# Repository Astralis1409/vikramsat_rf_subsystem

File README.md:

# VikramSAT RF Board
VikramSAT RF Board is the main communications board for the 'vikramsat', which is a 2U cubesat that me and my teammates are trying to make. This board also includes the RP2350A as the main data processing IC along with multiple interfaces. 

The RF transmitter on this board has an output Power of 4 Watts and it is not recommend to use this without a ham radio license. although you can receive data just fine.

It uses the CC1125 RF Transceiver from Texas Instruments as it's Transceiver and GSQ5111 Power Amplifier and it operates in the 70cm band. the RP2350A acts as a control IC for the CC1125 and this simplifies the process for the OnBoard Computer(the OBC of the cubesat)

# Why I chose to make this project
Me and my friends got an idea of making a cubesat about this time last year, and started learning all the electronics and design, and i am the leader of the group and i design the communications part. I chose to make this project in highway because this was the perfect time, as i was thinking about starting to make the pcb anf highway was announced, and surprisingly, only 4 hours are left from now until highway ends forever!

# Images
Kicanvas Link: [Here](https://kicanvas.org/?github=https%3A%2F%2Fgithub.com%2FKeyaan-07%2FVikramSat-RF-subsystem%2Ftree%2Fmain%2Fhardware_rf)

Files now have .STEP files!

# BOM
Final Breakdown at the bottom
|Id |Designator                                           |Designation                |Footprint                               |DNO|Price |Quantity|Amount |Link                                                                                                                                                                                        |
|---|-----------------------------------------------------|---------------------------|----------------------------------------|---|------|--------|-------|--------------------------------------------------------------------------------------------------------------------------------------------------------------------------------------------|
|1  |C1, C2, C32, C33                                     |15p                        |402                                     |Yes|0     |4       |0      |https://lcsc.com/product-detail/Multilayer-Ceramic-Capacitors-MLCC-SMD-SMT_Murata-Electronics-GJM1555C1H150FB01D_C441742.html                                                               |
|2  |C10                                                  |10n                        |402                                     |No |0.0008|100     |0.08   |https://lcsc.com/product-detail/Multilayer-Ceramic-Capacitors-MLCC-SMD-SMT_CCTC-TCC0402X7R103K500AT_C688874.html                                                                            |
|3  |C11, C12, C13, C15, C16, C3, C4, C5, C6, C7, C9      |47n                        |402                                     |No |0.0008|100     |0.08   |https://lcsc.com/product-detail/Multilayer-Ceramic-Capacitors-MLCC-SMD-SMT_CCTC-TCC0402X7R473M250AT_C5142571.html                                                                           |
|4  |C14                                                  |220n                       |402                                     |No |0.0016|100     |0.16   |https://lcsc.com/product-detail/Multilayer-Ceramic-Capacitors-MLCC-SMD-SMT_HRE-CGA0402X5R224K100GT_C7503518.html                                                                            |
|5  |C17, C18, C19, C21, C34, C35, C36, C39, C40          |4.7u                       |402                                     |No |0.014 |50      |0.7    |https://lcsc.com/product-detail/Multilayer-Ceramic-Capacitors-MLCC-SMD-SMT_Chinocera-HGC0402R5475M250NTEJ_C22367824.html                                                                    |
|6  |C20, C22, C23, C24, C25, C26, C27, C28, C29, C30, C31|100n                       |402                                     |Yes|0     |22      |0      |https://lcsc.com/product-detail/Multilayer-Ceramic-Capacitors-MLCC-SMD-SMT_Murata-Electronics-GRM155R61H104JE14D_C426067.html                                                               |
|7  |C37, C38                                             |100nF                      |402                                     |Yes|0     |4       |0      |https://lcsc.com/product-detail/Multilayer-Ceramic-Capacitors-MLCC-SMD-SMT_Murata-Electronics-GRM155R61H104JE14D_C426067.html                                                               |
|8  |C41, C42                                             |10u                        |805                                     |Yes|0     |2       |0      |https://lcsc.com/product-detail/Multilayer-Ceramic-Capacitors-MLCC-SMD-SMT_Samsung-Electro-Mechanics-CL21A106KBYQNNE_C2932476.html                                                          |
|9  |C43                                                  |1200p                      |402                                     |No |0.0009|100     |0.09   |https://lcsc.com/product-detail/Multilayer-Ceramic-Capacitors-MLCC-SMD-SMT_HRE-CGA0402X7R122K500GT_C22435964.html                                                                           |
|10 |C44                                                  |5p                         |402                                     |No |0.0009|1       |0.0009 |https://lcsc.com/product-detail/Multilayer-Ceramic-Capacitors-MLCC-SMD-SMT_HRE-CGA0402C0G5R0C500GT_C41361096.html                                                                           |
|11 |C45, C46, C47, C48, C49                              |220p                       |402                                     |No |0.0015|5       |0.0075 |https://lcsc.com/product-detail/Multilayer-Ceramic-Capacitors-MLCC-SMD-SMT_Walsin-0402N221J500CT_C301973.html                                                                               |
|12 |C8                                                   |1n8                        |402                                     |No |0.001 |100     |0.1    |https://lcsc.com/product-detail/Multilayer-Ceramic-Capacitors-MLCC-SMD-SMT_CCTC-TCC0402X7R182K500AT_C696873.html                                                                            |
|13 |D1                                                   |LED                        |402                                     |Yes|0     |1       |0      |https://lcsc.com/product-detail/LED-Indication-Discrete_Everlight-Elec-16-213-GHC-YR1S1N-3T_C2980183.html                                                                                   |
|14 |D2, D3                                               |D                          |402                                     |No |0.17  |5       |0.85   |https://lcsc.com/product-detail/Schottky-Diodes_onsemi-NSVR05F40NXT5G_C604383.html                                                                                                          |
|15 |DP1, DP2, DP3, DP4, DP5                              |~                          |Debug Pad                               |0  |0     |5       |0      |-                                                                                                                                                                                           |
|16 |IC1                                                  |CC1125RHBR                 |QFN50P500X500X100-33N-D                 |No |3.0257|2       |6.0514 |https://lcsc.com/product-detail/RF-Transceiver-ICs_TI-CC1125RHBR_C133234.html                                                                                                               |
|17 |IC2                                                  |BALF-SPI2-02D3             |BALFSPI202D3                            |No |0.41  |2       |0.82   |https://lcsc.com/product-detail/RF-Filters_ST-BALF-SPI2-02D3_C2688704.html                                                                                                                  |
|18 |IC3, IC4                                             |4259-63                    |PE4259                                  |No |0.6885|2       |1.377  |https://lcsc.com/product-detail/RF-Switches_pSemi-PE4259-63_C470892.html                                                                                                                    |
|19 |J1                                                   |Conn_Coaxial               |SMA_Amphenol_901-143_Horizontal         |No |0.4585|2       |0.917  |https://lcsc.com/product-detail/Coaxial-Connectors-RF_BAT-WIRELESS-BWSMA-KWE-Z001_C496551.html                                                                                              |
|20 |J2                                                   |Conn_01x03_Top_Bottom      |PinHeader_1x03_P2.54mm_Vertical         |Yes|0     |1       |0      |-                                                                                                                                                                                           |
|21 |J3                                                   |Conn_02x20_Top_Bottom      |PinHeader_2x20_P2.54mm_Vertical         |No |0.9305|2       |1.861  |https://lcsc.com/product-detail/Female-Headers_ZHOURI-PC104-2-20_C5307344.html                                                                                                              |
|22 |J4                                                   |USB_C_Receptacle_USB2.0_16P|USB_C_Receptacle_XKB_U262-16XN-4BVC11   |Yes|0     |1       |0      |https://lcsc.com/product-detail/USB-Connectors_SHOU-HAN-TYPE-C16PIN_C393939.html                                                                                                            |
|23 |L1                                                   |3.3u                       |IND-SMD_L2.0-W1.6_AOTA-B201610S3R3-101-T|No |0.28  |5       |1.4    |https://lcsc.com/product-detail/Power-Inductors_ABRACON-AOTA-B201610S3R3-101-T_C42411119.html                                                                                               |
|24 |R1                                                   |0                          |402                                     |0  |0     |1       |0      |Direct Bridge                                                                                                                                                                               |
|25 |R10, R11, R8, R9                                     |10k                        |402                                     |Yes|0.0278|20      |0.556  |https://lcsc.com/product-detail/Chip-Resistor-Surface-Mount_Vishay-Intertech-RCS040210K0FKED_C3020235.html                                                                                  |
|26 |R12, R6, R7                                          |1k                         |402                                     |No |0.0005|100     |0.05   |https://lcsc.com/product-detail/Chip-Resistor-Surface-Mount_FOJAN-FRC0402J102-TS_C2906899.html                                                                                              |
|27 |R2                                                   |56k                        |402                                     |No |0.0004|100     |0.04   |https://lcsc.com/product-detail/Chip-Resistor-Surface-Mount_FOJAN-FRC0402J563-TS_C2906955.html                                                                                              |
|28 |R3                                                   |33                         |402                                     |Yes|0     |1       |0      |https://lcsc.com/product-detail/Chip-Resistor-Surface-Mount_YAGEO-RT0402BRD0733RL_C852729.html                                                                                              |
|29 |R4, R5                                               |27                         |402                                     |Yes|0     |2       |0      |https://lcsc.com/product-detail/Chip-Resistor-Surface-Mount_PANASONIC-ERJ2GEJ270X_C278580.html                                                                                              |
|30 |R6,R7                                                |5.1k                       |402                                     |Yes|0     |2       |0      |https://lcsc.com/product-detail/Chip-Resistor-Surface-Mount_PANASONIC-ERJ2RKF5101X_C278598.html                                                                                             |
|31 |SW1                                                  |SW_Push                    |SW_SPST_PTS810                          |No |0.81  |2       |1.62   |https://lcsc.com/product-detail/Tactile-Switches_C-K-PTS810SJS250SMTRLFS_C221897.html?s_z=n_pts810                                                                                          |
|32 |U1                                                   |RP2350A-QFN60              |RP2350A_QFN-60_EP_7.75x7.75_Pitch0.4mm  |No |1.48  |3       |4.44   |https://www.silverlineelectronics.in/                                                                                                                                                       |
|33 |U2                                                   |W25Q128JVS                 |SOIC-8_5.3x5.3mm_P1.27mm                |No |1.77  |2       |3.54   |https://lcsc.com/product-detail/NOR-FLASH_Winbond-W25Q128JVSIM_C2613930.html?s_z=n_W25Q128JVS                                                                                               |
|34 |U3                                                   |GSQ5111                    |QFN-16_L3.0-W3.0-P0.50-TL-EP1.65        |No |4.75  |2       |9.5    |https://lcsc.com/product-detail/RF-Power-Amplifiers_GPowerTek-GSQ5111_C41410391.html                                                                                                        |
|35 |U4                                                   |SK5129                     |DFN-6_L1.6-W1.6-P0.50-BL-EP1.0          |No |0.1685|3       |0.5055 |https://lcsc.com/product-detail/Low-Noise-Amplifiers-LNA-RF_Suntek-SK5129_C5120312.html                                                                                                     |
|36 |U5                                                   |AMS1117s-3.3               |SOT-89-3                                |No |0.1057|5       |0.5285 |https://lcsc.com/product-detail/Voltage-Regulators-Linear-Low-Drop-Out-LDO-Regulators_JSMSEMI-AMS1117S-3-3_C917152.html?s_z=n_ams1117s                                                      |
|37 |Y1                                                   |Crystal_GND24              |Crystal_SMD_3225-4Pin_3.2x2.5mm         |No |0.45  |2       |0.9    |https://lcsc.com/product-detail/Crystal-Oscillators_Shenzhen-SCTF-Elec-SX3M40-000M20F30TNN_C2901588.html?s_z=s_Crystals%252C%2520Oscillators%252C%2520Resonators%257CCrystal%2520Oscillators|
|38 |Y2                                                   |Crystal_GND24              |Crystal_SMD_3225-4Pin_3.2x2.5mm         |No |0.43  |2       |0.86   |https://lcsc.com/product-detail/Crystals_ABRACON-ABM8-272-T3_C20625731.html?s_z=n_abm8-t272                                                                                                 |
|   |Shipping                                             |3.74                       |                                        |   |      |        |37.0348|                                                                                                                                                                                            |
|   |Merchandise total                                    |37.03                      |                                        |   |      |        |       |                                                                                                                                                                                            |
|   |pcb+stencil(jlcpcb)                                  |34.57                      |                                        |   |      |        |       |                                                                                                                                                                                            |
|   |Total                                                |75.34                      |                                        |   |      |        |       |                                                                                                                                                                                            |

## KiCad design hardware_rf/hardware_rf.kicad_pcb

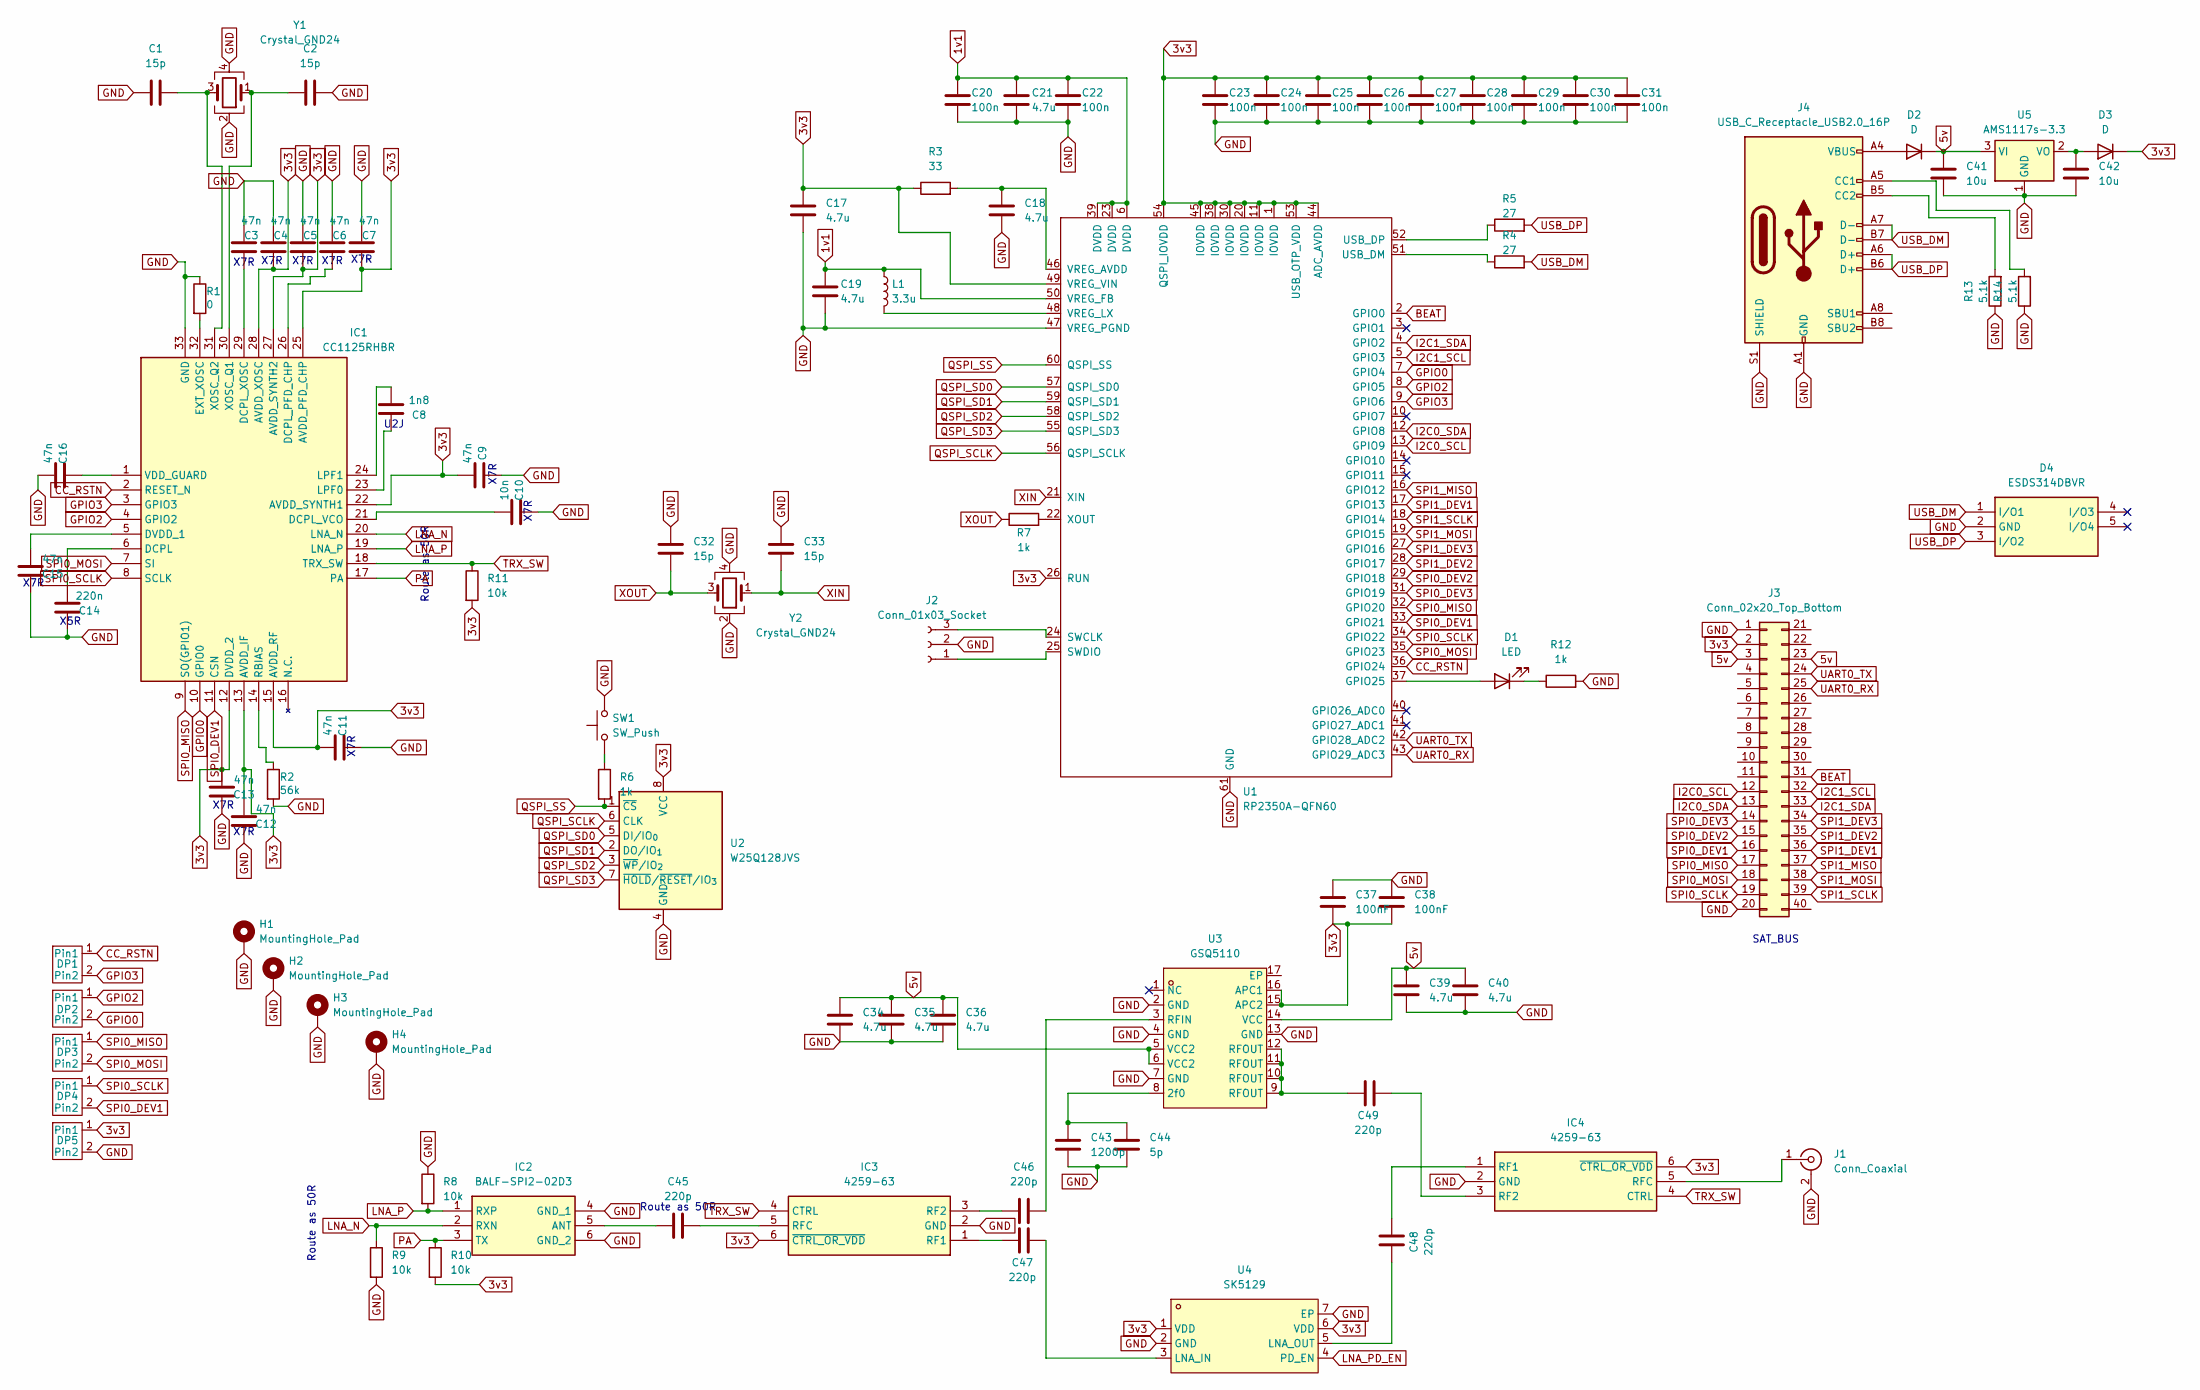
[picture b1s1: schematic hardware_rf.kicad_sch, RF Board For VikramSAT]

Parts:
C1, C2, C32, C33: 15p; C_0402_1005Metric
C3, C4, C5, C6, C7, C9, C11, C12, C13, C15, C16: 47n; C_0402_1005Metric
C8: 1n8; C_0402_1005Metric
C10: 10n; C_0402_1005Metric
C14: 220n; C_0402_1005Metric
C17, C18, C19, C21, C34, C35, C36, C39, C40: 4.7u; C_0402_1005Metric
C20, C22, C23, C24, C25, C26, C27, C28, C29, C30, C31: 100n; C_0402_1005Metric
C37, C38: 100nF; C_0402_1005Metric
C41, C42: 10u; C_0805_2012Metric
C43: 1200p; C_0402_1005Metric
C44: 5p; C_0402_1005Metric
C45, C46, C47, C48, C49: 220p; C_0402_1005Metric
D1: LED; LED_0402_1005Metric
D2, D3: D; D_0402_1005Metric
D4: ESDS314DBVR; ESDS314BVR_SOT95P280X145-5N; Mouser Part Number 595-ESDS314DBVR
DP1, DP2, DP3, DP4, DP5: Debug Pad
H1, H2, H3, H4: MountingHole_Pad; MountingHole_3mm_Pad_Via
IC1: CC1125RHBR; QFN50P500X500X100-33N-D; Mouser Part Number 595-CC1125RHBR
IC2: BALF-SPI2-02D3; BALFSPI202D3; Mouser Part Number 511-BALF-SPI2-02D3
IC3, IC4: 4259-63; PE4259; Mouser Part Number 81-4259-63
J1: Conn_Coaxial; SMA_Amphenol_901-143_Horizontal
J2: Conn_01x03_Socket; PinHeader_1x03_P2.54mm_Vertical
J3: Conn_02x20_Top_Bottom; PinHeader_2x20_P2.54mm_Vertical
J4: USB_C_Receptacle_USB2.0_16P; USB_C_Receptacle_XKB_U262-16XN-4BVC11
L1: 3.3u; IND-SMD_L2.0-W1.6_AOTA-B201610S3R3-101-T
R1: 0; R_0402_1005Metric
R2: 56k; R_0402_1005Metric
R3: 33; R_0402_1005Metric
R4, R5: 27; R_0402_1005Metric
R6, R7, R12: 1k; R_0402_1005Metric
R8, R9, R10, R11: 10k; R_0402_1005Metric
R13, R14: 5.1k; R_0402_1005Metric
SW1: SW_Push; SW_SPST_PTS810
U1: RP2350A-QFN60; RP2350A_QFN-60_EP_7.75x7.75_Pitch0.4mm
U2: W25Q128JVS; SOIC-8_5.3x5.3mm_P1.27mm
U3: GSQ5110; QFN-16_L3.0-W3.0-P0.50-TL-EP2.0; LCSC Part C41410390
U4: SK5129; DFN-6_L1.6-W1.6-P0.50-BL-EP1.0; LCSC Part C5120312
U5: AMS1117s-3.3; SOT-89-3
Y1, Y2: Crystal_GND24; Crystal_SMD_3225-4Pin_3.2x2.5mm

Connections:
1v1: C19.1, C20.1, C21.1, C22.1, L1.1, U1.6 (DVDD), U1.23 (DVDD), U1.39 (DVDD), U1.50 (VREG_FB)
3v3: C4.2, C5.2, C7.2, C9.1, C11.1, C12.1, C13.1, C17.1, C23.1, C24.1, C25.1, C26.1, C27.1, C28.1, C29.1, C30.1, C31.1, C37.2, C38.2, D3.1 (K), DP5.1 (Pin1), IC1.12 (DVDD_2), IC1.13 (AVDD_IF), IC1.15 (AVDD_RF), IC1.22 (AVDD_SYNTH1), IC1.25 (AVDD_PFD_CHP), IC1.27 (AVDD_SYNTH2), IC1.28 (AVDD_XOSC), IC3.6 (~CTRL_OR_VDD), IC4.6 (~CTRL_OR_VDD), J3.2, R3.1, R10.2, R11.2, U1.1 (IOVDD), U1.11 (IOVDD), U1.20 (IOVDD), U1.26 (RUN), U1.30 (IOVDD), U1.38 (IOVDD), U1.44 (ADC_AVDD), U1.45 (IOVDD), U1.49 (VREG_VIN), U1.53 (USB_OTP_VDD), U1.54 (QSPI_IOVDD), U2.8 (VCC), U3.15 (APC2), U3.16 (APC1), U4.1 (VDD), U4.6 (VDD)
5v: C34.1, C35.1, C36.1, C39.1, C40.1, C41.1, D2.1 (K), J3.3, J3.23, U3.5 (VCC2), U3.6 (VCC2), U3.14 (VCC), U5.3 (VI)
BEAT: J3.31, U1.2 (GPIO0)
CC_RSTN: DP1.1 (Pin1), IC1.2 (RESET_N), U1.36 (GPIO24)
GND: C1.2, C2.1, C3.1, C4.1, C5.1, C6.1, C7.1, C9.2, C10.2, C11.2, C12.2, C13.2, C14.2, C15.2, C16.1, C17.2, C18.2, C19.2, C20.2, C21.2, C22.2, C23.2, C24.2, C25.2, C26.2, C27.2, C28.2, C29.2, C30.2, C31.2, C32.1, C33.1, C34.2, C35.2, C36.2, C37.1, C38.1, C39.2, C40.2, C41.2, C42.2, C43.2, C44.2, D4.2 (GND), DP5.2 (Pin2), H1.1, H2.1, H3.1, H4.1, IC1.33 (GND), IC2.4 (GND_1), IC2.6 (GND_2), IC3.2 (GND), IC4.2 (GND), J1.2 (Ext), J2.2, J3.1, J3.20, J4.A1 (GND), J4.A12 (GND), J4.B1 (GND), J4.B12 (GND), J4.S1 (SHIELD), R1.1, R2.2, R8.1, R9.2, R12.2, R13.1, R14.1, SW1.2, U1.47 (VREG_PGND), U1.61 (GND), U2.4 (GND), U3.2 (GND), U3.4 (GND), U3.7 (GND), U3.13 (GND), U4.2 (GND), U4.7 (EP), U5.1 (GND), Y1.2, Y1.4, Y2.2, Y2.4
GPIO0: DP2.2 (Pin2), IC1.10 (GPIO0), U1.7 (GPIO4)
GPIO2: DP2.1 (Pin1), IC1.4 (GPIO2), U1.8 (GPIO5)
GPIO3: DP1.2 (Pin2), IC1.3 (GPIO3), U1.9 (GPIO6)
I2C0_SCL: J3.12, U1.13 (GPIO9)
I2C0_SDA: J3.13, U1.12 (GPIO8)
I2C1_SCL: J3.32, U1.5 (GPIO3)
I2C1_SDA: J3.33, U1.4 (GPIO2)
LNA_N: IC1.20 (LNA_N), IC2.2 (RXN), R9.1
LNA_P: IC1.19 (LNA_P), IC2.1 (RXP), R8.2
LNA_PD_EN: U4.4 (PD_EN)
unnamed: C49.1, U3.9 (RFOUT), U3.10 (RFOUT), U3.11 (RFOUT), U3.12 (RFOUT)
unnamed: D1.2 (A), U1.37 (GPIO25)
unnamed: D1.1 (K), R12.1
unnamed: D2.2 (A), J4.A4 (VBUS), J4.A9 (VBUS), J4.B4 (VBUS), J4.B9 (VBUS)
unnamed: C42.1, D3.2 (A), U5.2 (VO)
unnamed: C14.1, IC1.6 (DCPL)
unnamed: C6.2, IC1.26 (DCPL_PFD_CHP)
unnamed: C10.1, IC1.21 (DCPL_VCO)
unnamed: C3.2, IC1.29 (DCPL_XOSC)
unnamed: C15.1, IC1.5 (DVDD_1)
unnamed: IC1.32 (EXT_XOSC), R1.2
unnamed: C8.2, IC1.23 (LPF0)
unnamed: C8.1, IC1.24 (LPF1)
unnamed: IC1.14 (RBIAS), R2.1
unnamed: C16.2, IC1.1 (VDD_GUARD)
unnamed: C2.2, IC1.30 (XOSC_Q1), Y1.1
unnamed: C1.1, IC1.31 (XOSC_Q2), Y1.3
unnamed: C45.1, IC2.5 (ANT)
unnamed: C47.1, IC3.1 (RF1)
unnamed: C46.1, IC3.3 (RF2)
unnamed: C45.2, IC3.5 (RFC)
unnamed: C48.2, IC4.1 (RF1)
unnamed: C49.2, IC4.3 (RF2)
unnamed: IC4.5 (RFC), J1.1 (In)
unnamed: J2.1, U1.25 (SWDIO)
unnamed: J2.3, U1.24 (SWCLK)
unnamed: J4.A5 (CC1), R14.2
unnamed: J4.B5 (CC2), R13.2
unnamed: R6.1, SW1.1
unnamed: R4.1, U1.51 (USB_DM)
unnamed: R5.1, U1.52 (USB_DP)
unnamed: C18.1, R3.2, U1.46 (VREG_AVDD)
unnamed: L1.2, U1.48 (VREG_LX)
unnamed: R7.2, U1.22 (XOUT)
unnamed: C43.1, C44.1, U3.8 (2f0)
unnamed: C46.2, U3.3 (RFIN)
unnamed: C47.2, U4.3 (LNA_IN)
unnamed: C48.1, U4.5 (LNA_OUT)
PA: IC1.17 (PA), IC2.3 (TX), R10.1
QSPI_SCLK: U1.56 (QSPI_SCLK), U2.6 (CLK)
QSPI_SD0: U1.57 (QSPI_SD0), U2.5 (DI/IO_{0})
QSPI_SD1: U1.59 (QSPI_SD1), U2.2 (DO/IO_{1})
QSPI_SD2: U1.58 (QSPI_SD2), U2.3 (~WP/IO_{2})
QSPI_SD3: U1.55 (QSPI_SD3), U2.7 (~HOLD/~RESET/IO_{3})
QSPI_SS: R6.2, U1.60 (QSPI_SS), U2.1 (~CS)
SPI0_DEV1: DP4.2 (Pin2), IC1.11 (CSN), J3.16, U1.33 (GPIO21)
SPI0_DEV2: J3.15, U1.29 (GPIO18)
SPI0_DEV3: J3.14, U1.31 (GPIO19)
SPI0_MISO: DP3.1 (Pin1), IC1.9 (SO(GPIO1)), J3.17, U1.32 (GPIO20)
SPI0_MOSI: DP3.2 (Pin2), IC1.7 (SI), J3.18, U1.35 (GPIO23)
SPI0_SCLK: DP4.1 (Pin1), IC1.8 (SCLK), J3.19, U1.34 (GPIO22)
SPI1_DEV1: J3.36, U1.17 (GPIO13)
SPI1_DEV2: J3.35, U1.28 (GPIO17)
SPI1_DEV3: J3.34, U1.27 (GPIO16)
SPI1_MISO: J3.37, U1.16 (GPIO12)
SPI1_MOSI: J3.38, U1.19 (GPIO15)
SPI1_SCLK: J3.39, U1.18 (GPIO14)
TRX_SW: IC1.18 (TRX_SW), IC3.4 (CTRL), IC4.4 (CTRL), R11.1
UART0_RX: J3.25, U1.43 (GPIO29_ADC3)
UART0_TX: J3.24, U1.42 (GPIO28_ADC2)
USB_DM: D4.1 (I/O1), J4.A7 (D-), J4.B7 (D-), R4.2
USB_DP: D4.3 (I/O2), J4.A6 (D+), J4.B6 (D+), R5.2
XIN: C33.2, U1.21 (XIN), Y2.1
XOUT: C32.2, R7.1, Y2.3

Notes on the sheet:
Route as 50R
X7R
X5R
SAT_BUS
U2J

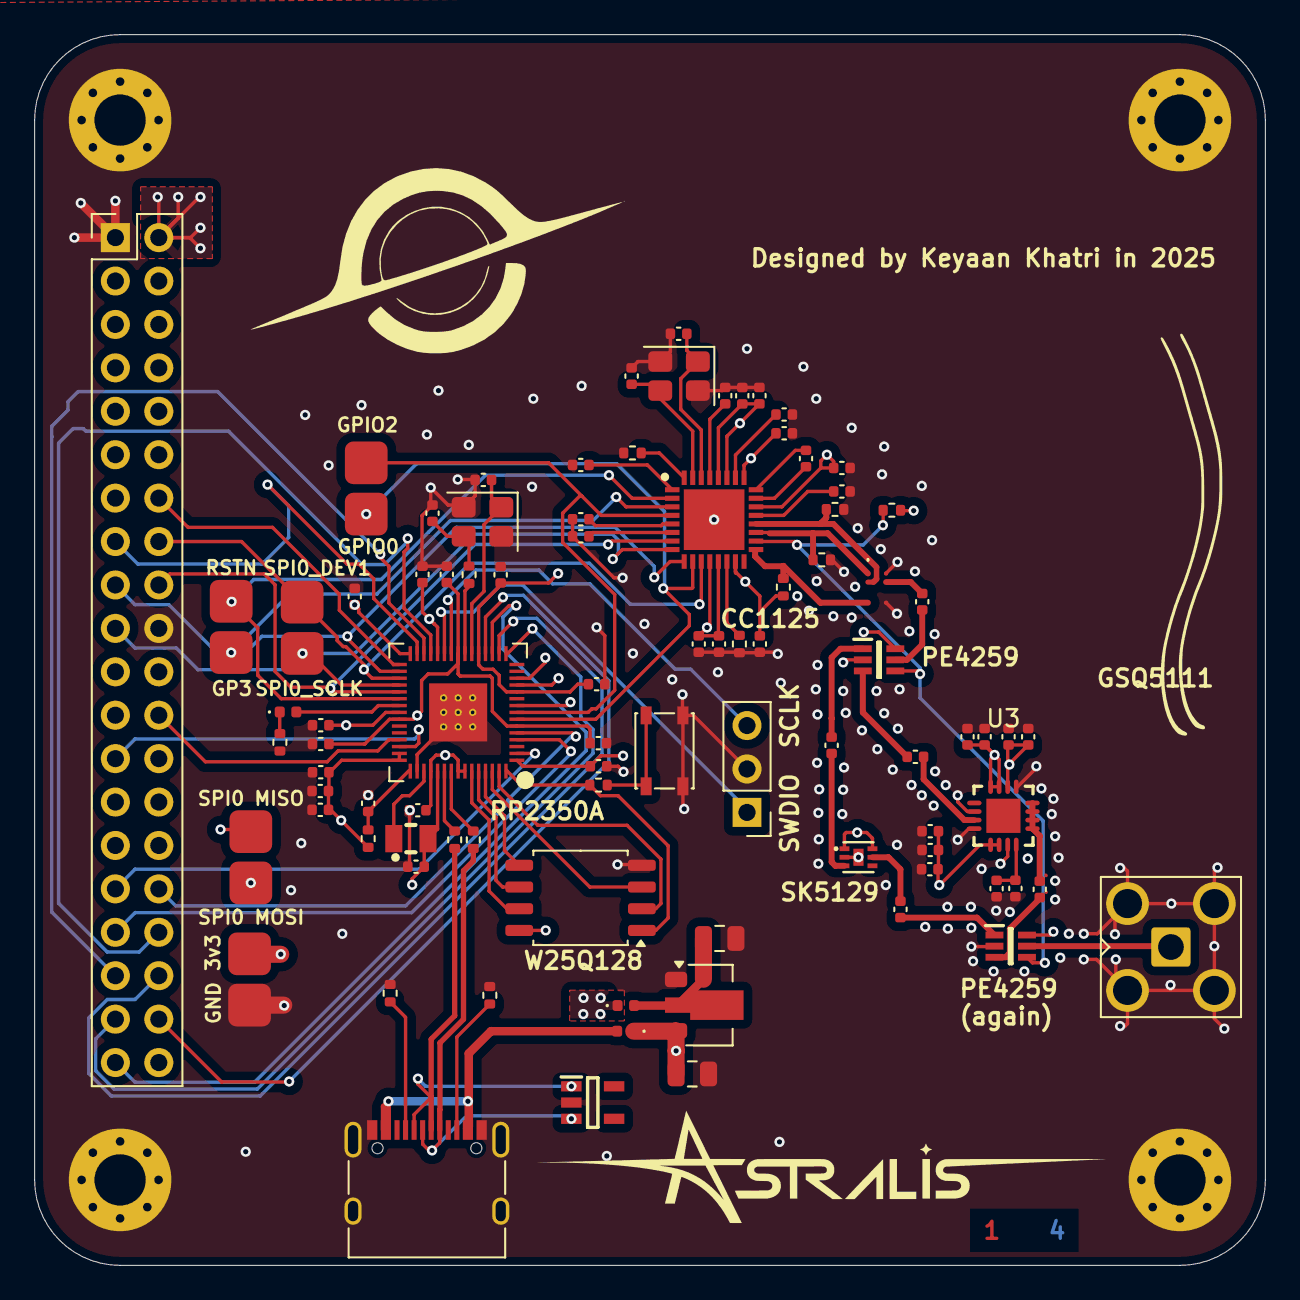
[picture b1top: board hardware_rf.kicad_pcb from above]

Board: 4 copper layers, 72.0 x 72.0 mm, 93 parts (0 on the bottom side), 79 nets.

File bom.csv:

Id,Designator,Designation,Footprint,DNO,Price,Quantity,Amount,Link
1,"C1, C2, C32, C33",15p,402,Yes,0,4,0,https://lcsc.com/product-detail/Multilayer-Ceramic-Capacitor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
2,C10,10n,402,No,0.0008,100,0.08,https://lcsc.com/product-detail/Multilayer-Ceramic-Capacitor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
3,"C11, C12, C13, C15, C16, C3, C4, C5, C6, C7, C9",47n,402,No,0.0008,100,0.08,https://lcsc.com/product-detail/Multilayer-Ceramic-Capacitor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
4,C14,220n,402,No,0.0016,100,0.16,https://lcsc.com/product-detail/Multilayer-Ceramic-Capacitor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
5,"C17, C18, C19, C21, C34, C35, C36, C39, C40",4.7u,402,No,0.014,50,0.7,https://lcsc.com/product-detail/Multilayer-Ceramic-Capacitor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
6,"C20, C22, C23, C24, C25, C26, C27, C28, C29, C30, C31",100n,402,Yes,0,22,0,https://lcsc.com/product-detail/Multilayer-Ceramic-Capacitor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
7,"C37, C38",100nF,402,Yes,0,4,0,https://lcsc.com/product-detail/Multilayer-Ceramic-Capacitor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
8,"C41, C42",10u,805,Yes,0,2,0,https://lcsc.com/product-detail/Multilayer-Ceramic-Capacitor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
9,C43,1200p,402,No,0.0009,100,0.09,https://lcsc.com/product-detail/Multilayer-Ceramic-Capacitor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
10,C44,5p,402,No,0.0009,1,0.0009,https://lcsc.com/product-detail/Multilayer-Ceramic-Capacitor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
11,"C45, C46, C47, C48, C49",220p,402,No,0.0015,5,0.0075,https://lcsc.com/product-detail/Multilayer-Ceramic-Capacitor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
12,C8,1n8,402,No,0.001,100,0.1,https://lcsc.com/product-detail/Multilayer-Ceramic-Capacitor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
13,D1,LED,402,Yes,0,1,0,https://lcsc.com/product-detail/LED-Indication-Discrete_Ever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
14,"D2, D3",D,402,No,0.17,5,0.85,https://lcsc.com/product-detail/Schottky-Diodes_onsemi-NSVR0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
15,"DP1, DP2, DP3, DP4, DP5",~,Debug Pad,0,0,5,0,-
16,IC1,CC1125RHBR,QFN50P500X500X100-33N-D,No,3.0257,2,6.0514,https://lcsc.com/product-detail/RF-Transceiver-ICs_TI-CC1125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
17,IC2,BALF-SPI2-02D3,BALFSPI202D3,No,0.41,2,0.82,https://lcsc.com/product-detail/RF-Filters_ST-BALF-SPI2-02D3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
18,"IC3, IC4",4259-63,PE4259,No,0.6885,2,1.377,https://lcsc.com/product-detail/RF-Switches_pSemi-PE4259-63_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
19,J1,Conn_Coaxial,SMA_Amphenol_901-143_Horizontal,No,0.4585,2,0.917,https://lcsc.com/product-detail/Coaxial-Connectors-RF_BAT-WI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
20,J2,Conn_01x03_Top_Bottom,PinHeader_1x03_P2.54mm_Vertical,Yes,0,1,0,-
21,J3,Conn_02x20_Top_Bottom,PinHeader_2x20_P2.54mm_Vertical,No,0.9305,2,1.861,https://lcsc.com/product-detail/Female-Headers_ZHOURI-PC104-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
22,J4,USB_C_Receptacle_USB2.0_16P,USB_C_Receptacle_XKB_U262-16XN-4BVC11,Yes,0,1,0,https://lcsc.com/product-detail/USB-Connectors_SHOU-HAN-TYPE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
23,L1,3.3u,IND-SMD_L2.0-W1.6_AOTA-B201610S3R3-101-T,No,0.28,5,1.4,https://lcsc.com/product-detail/Power-Inductors_ABRACON-AOTA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
24,R1,0,402,0,0,1,0,Direct Bridge
25,"R10, R11, R8, R9",10k,402,Yes,0.0278,20,0.556,https://lcsc.com/product-detail/Chip-Resistor-Surface-Mount_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
26,"R12, R6, R7",1k,402,No,0.0005,100,0.05,https://lcsc.com/product-detail/Chip-Resistor-Surface-Mount_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
27,R2,56k,402,No,0.0004,100,0.04,https://lcsc.com/product-detail/Chip-Resistor-Surface-Mount_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
28,R3,33,402,Yes,0,1,0,https://lcsc.com/product-detail/Chip-Resistor-Surface-Mount_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
29,"R4, R5",27,402,Yes,0,2,0,https://lcsc.com/product-detail/Chip-Resistor-Surface-Mount_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
30,"R6,R7",5.1k,402,Yes,0,2,0,https://lcsc.com/product-detail/Chip-Resistor-Surface-Mount_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
31,SW1,SW_Push,SW_SPST_PTS810,No,0.81,2,1.62,https://lcsc.com/product-detail/Tactile-Switches_C-K-PTS810S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
32,U1,RP2350A-QFN60,RP2350A_QFN-60_EP_7.75x7.75_Pitch0.4mm,No,1.48,3,4.44,https://www.silverlineelectronics.in/
33,U2,W25Q128JVS,SOIC-8_5.3x5.3mm_P1.27mm,No,1.77,2,3.54,https://lcsc.com/product-detail/NOR-FLASH_Winbond-W25Q128JVS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
34,U3,GSQ5111,QFN-16_L3.0-W3.0-P0.50-TL-EP1.65,No,4.75,2,9.5,https://lcsc.com/product-detail/RF-Power-Amplifiers_GPowerTe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
35,U4,SK5129,DFN-6_L1.6-W1.6-P0.50-BL-EP1.0,No,0.1685,3,0.5055,https://lcsc.com/product-detail/Low-Noise-Amplifiers-LNA-RF_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
36,U5,AMS1117s-3.3,SOT-89-3,No,0.1057,5,0.5285,https://lcsc.com/product-detail/Voltage-Regulators-Linear-Lo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
37,Y1,Crystal_GND24,Crystal_SMD_3225-4Pin_3.2x2.5mm,No,0.45,2,0.9,https://lcsc.com/product-detail/Crystal-Oscillators_Shenzhen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
38,Y2,Crystal_GND24,Crystal_SMD_3225-4Pin_3.2x2.5mm,No,0.43,2,0.86,https://lcsc.com/product-detail/Crystals_ABRACON-ABM8-272-T3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
,Shipping,3.74,,,,,37.0348,
,Merchandise total,37.03,,,,,,
,pcb+stencil(jlcpcb),34.57,,,,,,
,Total,75.34,,,,,,

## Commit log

2025-07-02 'first'
2025-07-02 Second
2025-07-10 'journaling'
2025-07-10 'journal'
2025-07-10 journaling
2025-07-10 pcb+journal
2025-07-10 images
2025-07-10 schematic work
2025-07-10 journal
2025-07-19 Backups
2025-07-21 gallery add
2025-07-21 new footprint
2025-07-21 symbol
2025-07-22 Create LICENSE
2025-07-24 schematic
2025-07-24 footprint
2025-07-30 Schematic Done
2025-07-30 assignment
2025-07-30 added images
2025-07-30 Assignment of footprints
2025-07-31 layout
2025-07-31 pcb components added
2025-07-31 Pcb Done
2025-07-31 add bom
2025-07-31 make readme
2025-07-31 README
2025-07-31 images added
2025-08-01 schematic.pdf
2025-08-01 CC lines on USB fixed
2025-08-01 update bom
2025-08-01 step addition
2025-08-02 Added SWD Header
2025-08-02 Update images with SWD
2025-08-02 Added SWD to PCB
2025-08-02 Added SWD
2025-08-02 Kicanvas Link
2025-08-02 3d Model add
2025-08-03 Update USB Connector pos
2025-08-03 Update USB C Position
2025-08-16 added ESD Protection and Moved USB-C Connector pos
2025-08-16 ibom
2025-08-16 Update PA
